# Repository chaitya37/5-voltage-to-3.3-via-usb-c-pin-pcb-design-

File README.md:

# USB-C 5V/3.3V Power Module

A compact power supply board that takes USB-C 5V input and provides regulated 5V (passthrough) and 3.3V outputs, with an onboard LED indicator for the 3.3V rail. Designed in KiCad.

## Specs

| Parameter | Value |
|---|---|
| Input | USB-C, 5V (default profile, no PD/QC negotiation) |
| Output 1 | 5V passthrough, up to ~1A |
| Output 2 | 3.3V regulated (AMS1117-3.3), up to ~500mA |
| PCB | 2-layer |

## PCB Layout

## Schematic

See [schematic.pdf](schematic.pdf) for the full schematic.

## Design Notes

- **CC1/CC2 (5.1kΩ to GND):** Required per USB Type-C spec so the source negotiates default 5V/900mA-1.5A power — without these the connector won't output any power at all.
- **AMS1117-3.3 regulator:** Chosen for simplicity and wide availability. Input/output capacitors (10µF each) placed close to the IC per datasheet recommendations for stability.
- **LED indicator:** Wired in parallel off the 3.3V rail (not in series with the output header) through a 330Ω resistor, so it only lights when the regulator is actually working correctly — doubles as a quick diagnostic.
- **Shield grounding:** USB-C shield tab tied to GND through a 330Ω resistor for basic ESD/EMI mitigation.
- **Ground plane:** Bottom-layer copper pour tied to all GND pads via 4 vias, reducing return path resistance and simplifying top-layer routing.

## Bill of Materials

Full BOM: [Buck 5 to 3.3v via usb c.csv](Buck%205%20to%203.3v%20via%20usb%20c.csv)

| Ref | Component | Value/Part | Footprint |
|---|---|---|---|
| J1 | USB-C Receptacle | HRO TYPE-C-31-M-12 | USB_C_Receptacle_HRO_TYPE-C-31-M-12 |
| J2 | Pin Header | 1x3, 2.54mm | PinHeader_1x03_P2.54mm_Vertical |
| U1 | LDO Regulator | AMS1117-3.3 | SOT-223-3_TabPin2 |
| R1, R2 | Resistor | 5.1kΩ | R_0805_2012Metric |
| R3, R4 | Resistor | 330Ω | R_0805_2012Metric |
| C1, C2 | Capacitor | 10µF | C_1206_3216Metric |
| D1 | LED | Generic | LED_0805_2012Metric |

## Files

- [`Buck 5 to 3.3v via usb c.kicad_sch`](Buck%205%20to%203.3v%20via%20usb%20c.kicad_sch) — KiCad schematic source
- [`Buck 5 to 3.3v via usb c.kicad_pcb`](Buck%205%20to%203.3v%20via%20usb%20c.kicad_pcb) — KiCad PCB source
- [`schematic.pdf`](schematic.pdf) — Exported schematic
- [`gerber.zip`](gerber.zip) — Fabrication-ready Gerber files (JLCPCB/PCBWay compatible)
- [`drill.zip`](drill.zip) — Drill files
- [`Buck 5 to 3.3v via usb c.csv`](Buck%205%20to%203.3v%20via%20usb%20c.csv) — Bill of materials

> Note: fab files are provided as `.zip` — most fab houses and browsers don't handle `.rar` well, so use the zipped versions.

## Status

Designed and DRC-clean (0 violations, 0 unconnected nets). Boards ordered for fabrication — photos and test results to be added once assembled.

## License

MIT — feel free to use, modify, or build on this design.

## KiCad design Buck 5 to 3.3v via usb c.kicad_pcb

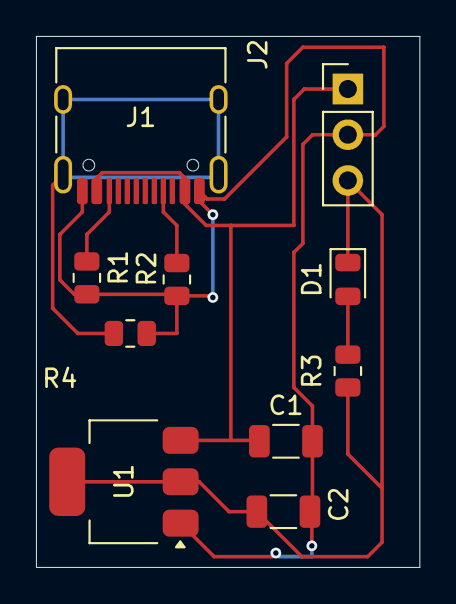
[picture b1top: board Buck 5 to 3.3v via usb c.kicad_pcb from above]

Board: 2 copper layers, 21.3 x 29.5 mm, 10 parts (0 on the bottom side), 7 nets.

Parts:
C1, C2: 10 microF; C_1206_3216Metric
D1: LED; LED_0805_2012Metric
J1: USB_C; USB_C_Receptacle_HRO_TYPE-C-31-M-12
J2: Conn_01x03_Pin; PinHeader_1x03_P2.54mm_Vertical
R1, R2: 5.1 kohm; R_0805_2012Metric
R3, R4: 330 ohm; R_0805_2012Metric
U1: AMS1117-3.3; SOT-223-3_TabPin2

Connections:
/3.3 voltage: C2.1, D1.1 (K), J2.3, R3.1, U1.2 (VO)
/5 voltage: C1.1, J1.A4 (VBUS), J1.A9 (VBUS), J1.B4 (VBUS), J1.B9 (VBUS), J2.1, U1.3 (VI)
GND: C1.2, C2.2, J1.A1 (GND), J1.A12 (GND), J1.B1 (GND), J1.B12 (GND), J2.2, R1.2, R2.2, R4.2, U1.1 (GND)
unnamed: D1.2 (A), R3.2
unnamed: J1.A5 (CC1), R2.1
unnamed: J1.B5 (CC2), R1.1
unnamed: J1.SH, R4.1
